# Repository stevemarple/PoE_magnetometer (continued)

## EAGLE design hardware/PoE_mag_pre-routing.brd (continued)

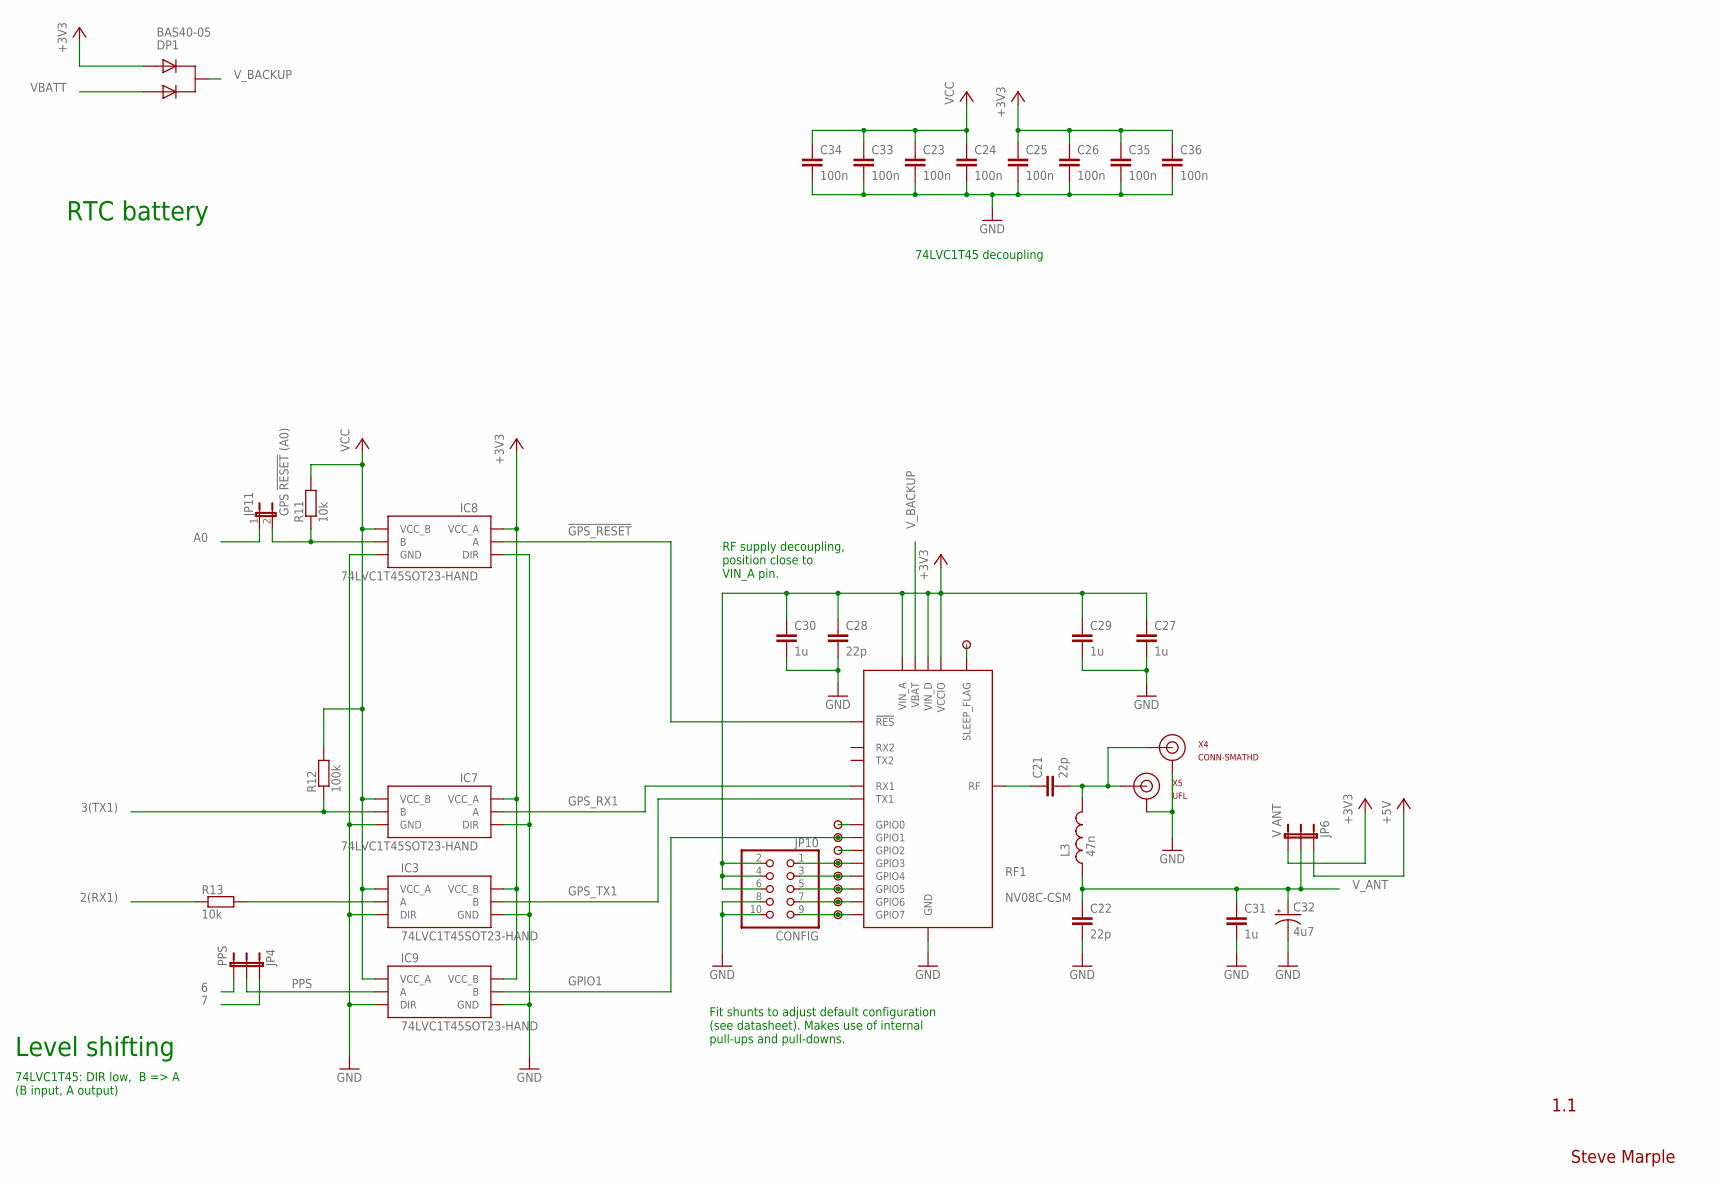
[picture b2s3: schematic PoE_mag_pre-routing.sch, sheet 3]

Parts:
C21, C22, C28: 22p; 0805-HAND
C23, C24, C25, C26, C33, C34, C35, C36: 100n; 1206-HAND
C27, C29, C30, C31: 1u; 1206-HAND
C32: 4u7; CPOL-RADIAL-10UF-25V
DP1: BAS40-05; SOT23-3-HAND
IC3, IC7, IC8, IC9: 74LVC1T45SOT23-HAND; SOT23-6-HAND
JP4: PPS; 1X03
JP6: V ANT; 1X03
JP10: CONFIG; 2X05
JP11: GPS !RESET! (A0); 1X02
L3: 47n; 0805-HAND
R11, R13: 10k; 1206-HAND
R12: 100k; 1206-HAND
RF1: NV08C-CSM; NVC08C-CSM-HAND
U$2, U$3, U$4, U$6, U$7, U$8, U$9, U$10: PAD
U$5: ?; PAD
X4: CONN-SMATHD; SMA-THD
X5: UFL; CONN-UFL-HAND-SOLDERING

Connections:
2(RX1): R13.1; also elsewhere on the board
3(TX1): IC7.4 (B), R12.1; also elsewhere on the board
6: JP4.3; also elsewhere on the board
7: JP4.1; also elsewhere on the board
!GPS_RESET: IC8.3 (A), RF1.P$25 (!RES)
+3V3: C25.1, C26.1, C27.1, C28.1, C29.1, C30.1, C35.1, C36.1, DP1.2 (A2), IC3.6 (VCC_B), IC7.1 (VCC_A), IC8.1 (VCC_A), IC9.6 (VCC_B), JP6.3, JP10.2, JP10.4, JP10.6, RF1.P$8 (VIN_A), RF1.P$26 (VIN_D), RF1.P$28 (VCCIO); also elsewhere on the board
+5V: JP6.1; also elsewhere on the board
A0: JP11.1; also elsewhere on the board
GND: C22.2, C23.2, C24.2, C25.2, C26.2, C27.2, C28.2, C29.2, C30.2, C31.2, C32.2 (-), C33.2, C34.2, C35.2, C36.2, IC3.2 (GND), IC3.5 (DIR), IC7.2 (GND), IC7.5 (DIR), IC8.2 (GND), IC8.5 (DIR), IC9.2 (GND), IC9.5 (DIR), JP10.8, JP10.10, RF1.P$3 (GND), RF1.P$9 (GND), RF1.P$10 (GND), RF1.P$11 (GND), RF1.P$12 (GND), RF1.P$13 (GND), RF1.P$14 (GND), RF1.P$16 (GND), RF1.P$17 (GND), RF1.P$18 (GND), RF1.P$19 (GND), RF1.P$22 (GND), RF1.P$24 (GND), RF1.P$27 (GND), RF1.P$29 (GND), RF1.P$34 (GND), X4.GND@0 (GND), X4.GND@1 (GND), X4.GND@2 (GND), X4.GND@3 (GND), X5.GND@0 (GND), X5.GND@1 (GND); also elsewhere on the board
GPIO0: RF1.P$20 (GPIO0), U$3.1
GPIO1: IC9.4 (B), RF1.P$2 (GPIO1), U$4.1
GPIO2: RF1.P$1 (GPIO2), U$5.1
GPIO3: JP10.1, RF1.P$6 (GPIO3), U$6.1
GPIO4: JP10.3, RF1.P$7 (GPIO4), U$7.1
GPIO5: JP10.5, RF1.P$4 (GPIO5), U$8.1
GPIO6: JP10.7, RF1.P$35 (GPIO6), U$9.1
GPIO7: JP10.9, RF1.P$5 (GPIO7), U$10.1
GPS_RX1: IC7.3 (A), RF1.P$33 (RX1)
GPS_TX1: IC3.4 (B), RF1.P$32 (TX1)
unnamed: IC8.4 (B), JP11.2, R11.1
unnamed: C21.2, L3.2, X4.SIG (SIGNAL), X5.SIGNAL
unnamed: C21.1, RF1.P$15 (RF)
unnamed: IC3.3 (A), R13.2
PPS: IC9.3 (A), JP4.2
SLEEP_FLAG: RF1.P$21 (SLEEP_FLAG), U$2.1
VBATT: DP1.1 (A1); also elsewhere on the board
VCC: C23.1, C24.1, C33.1, C34.1, IC3.1 (VCC_A), IC7.6 (VCC_B), IC8.6 (VCC_B), IC9.1 (VCC_A), R11.2, R12.2; also elsewhere on the board
V_ANT: C22.1, C31.1, C32.1 (+), JP6.2, L3.1
V_BACKUP: DP1.3 (C), RF1.P$23 (VBAT)

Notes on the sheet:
1.1
Steve Marple
Level shifting
RTC battery
74LVC1T45: DIR low, B => A (B input, A output)
RF supply decoupling, position close to VIN_A pin.
Fit shunts to adjust default configuration (see datasheet). Makes use of internal pull-ups and pull-downs.
74LVC1T45 decoupling

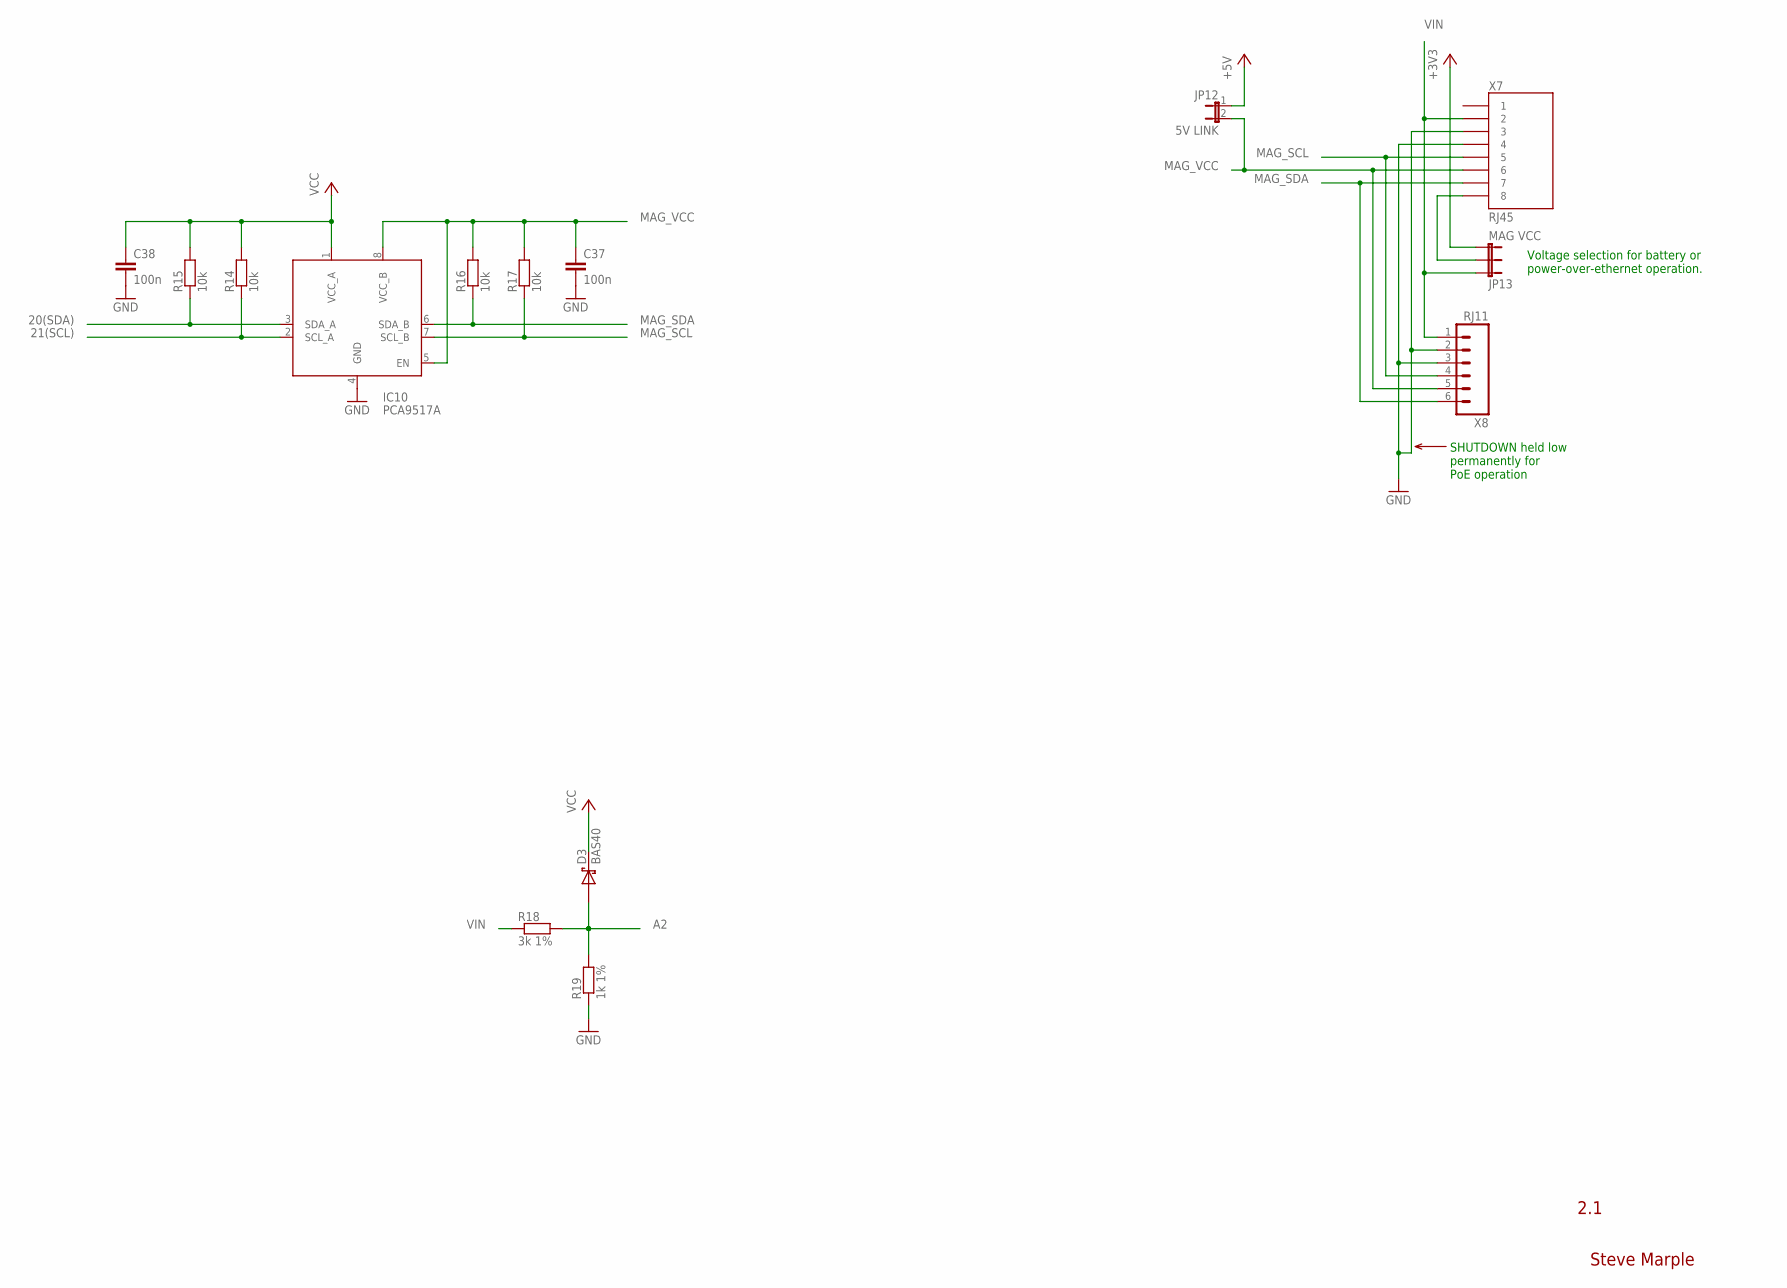
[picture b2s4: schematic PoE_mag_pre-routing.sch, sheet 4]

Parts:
C37, C38: 100n; 1206-HAND
D3: BAS40; SOT23-3-HAND
IC10: PCA9517A; SO08
JP12: 5V LINK; 1X02
JP13: MAG VCC; 1X03
R14, R15, R16, R17: 10k; 1206-HAND
R18: 3k 1%; 1206-HAND
R19: 1k 1%; 1206-HAND
X7: RJ45; RJ45-8
X8: RJ11; RJ11-6

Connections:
20(SDA): IC10.3 (SDA_A), R15.1; also elsewhere on the board
21(SCL): IC10.2 (SCL_A), R14.1; also elsewhere on the board
+3V3: JP13.3; also elsewhere on the board
+5V: JP12.1; also elsewhere on the board
A2: D3.1 (A), R18.2, R19.2; also elsewhere on the board
GND: C37.2, C38.2, IC10.4 (GND), R19.1, X7.3, X7.4, X8.2, X8.3; also elsewhere on the board
MAG_SCL: IC10.7 (SCL_B), R17.1, X7.5, X8.4
MAG_SDA: IC10.6 (SDA_B), R16.1, X7.7, X8.6
MAG_VCC: C37.1, IC10.5 (EN), IC10.8 (VCC_B), JP12.2, R16.2, R17.2, X7.6, X8.5
unnamed: JP13.2, X7.8
VCC: C38.1, D3.3 (C), IC10.1 (VCC_A), R14.2, R15.2; also elsewhere on the board
VIN: JP13.1, R18.1, X7.2, X8.1; also elsewhere on the board

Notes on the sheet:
2.1
Steve Marple
Voltage selection for battery or power-over-ethernet operation.
SHUTDOWN held low permanently for PoE operation

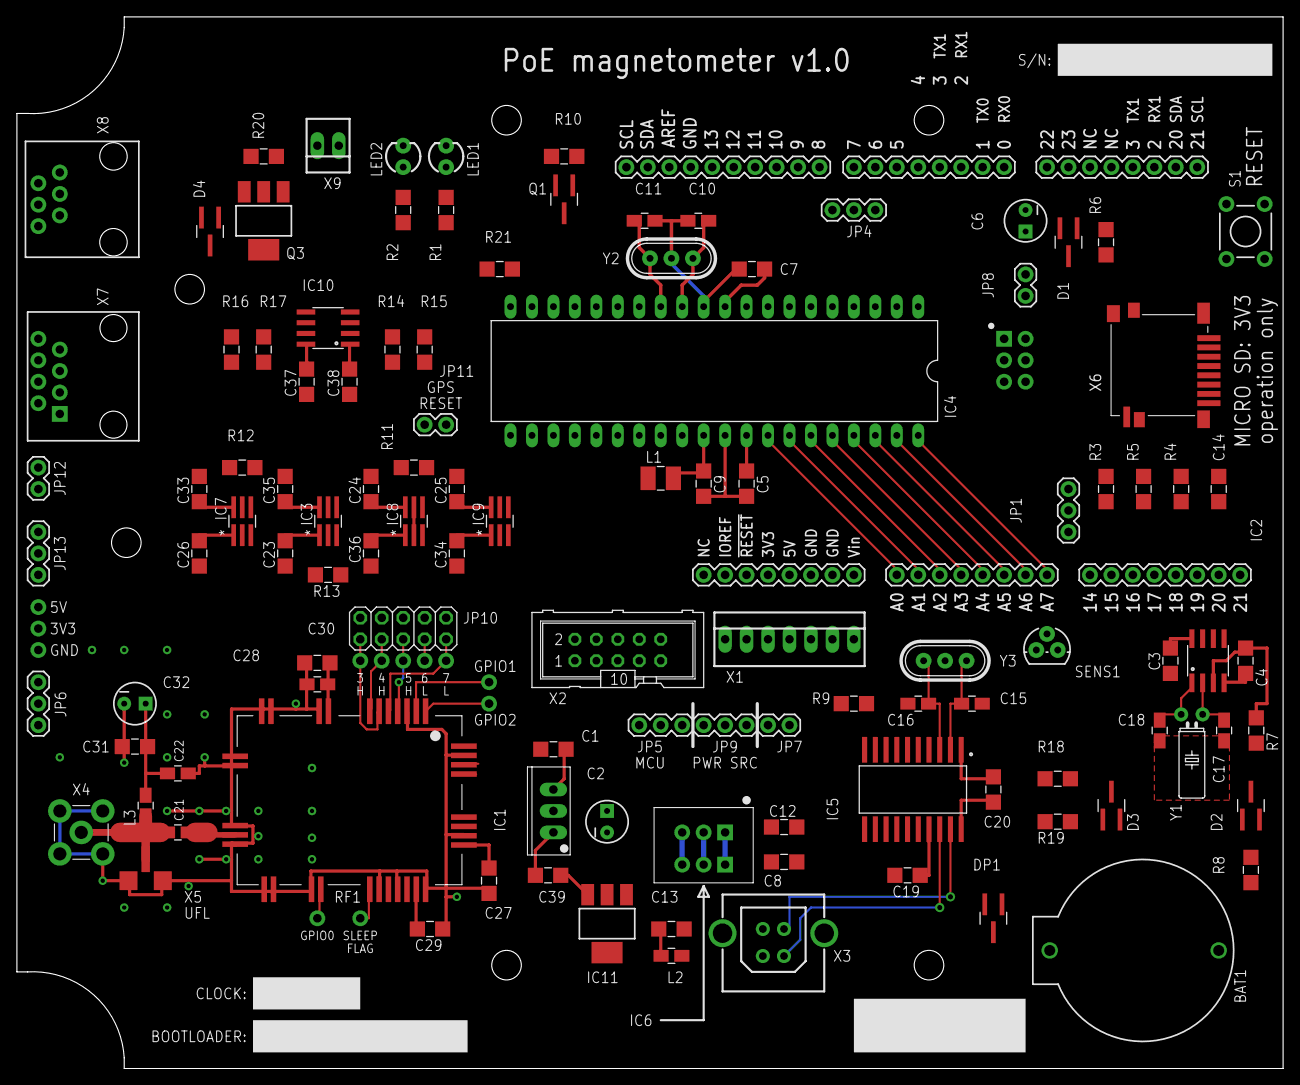
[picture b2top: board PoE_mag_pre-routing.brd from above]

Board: 2 copper layers, 149.9 x 124.5 mm, 124 parts (0 on the bottom side), 87 nets.

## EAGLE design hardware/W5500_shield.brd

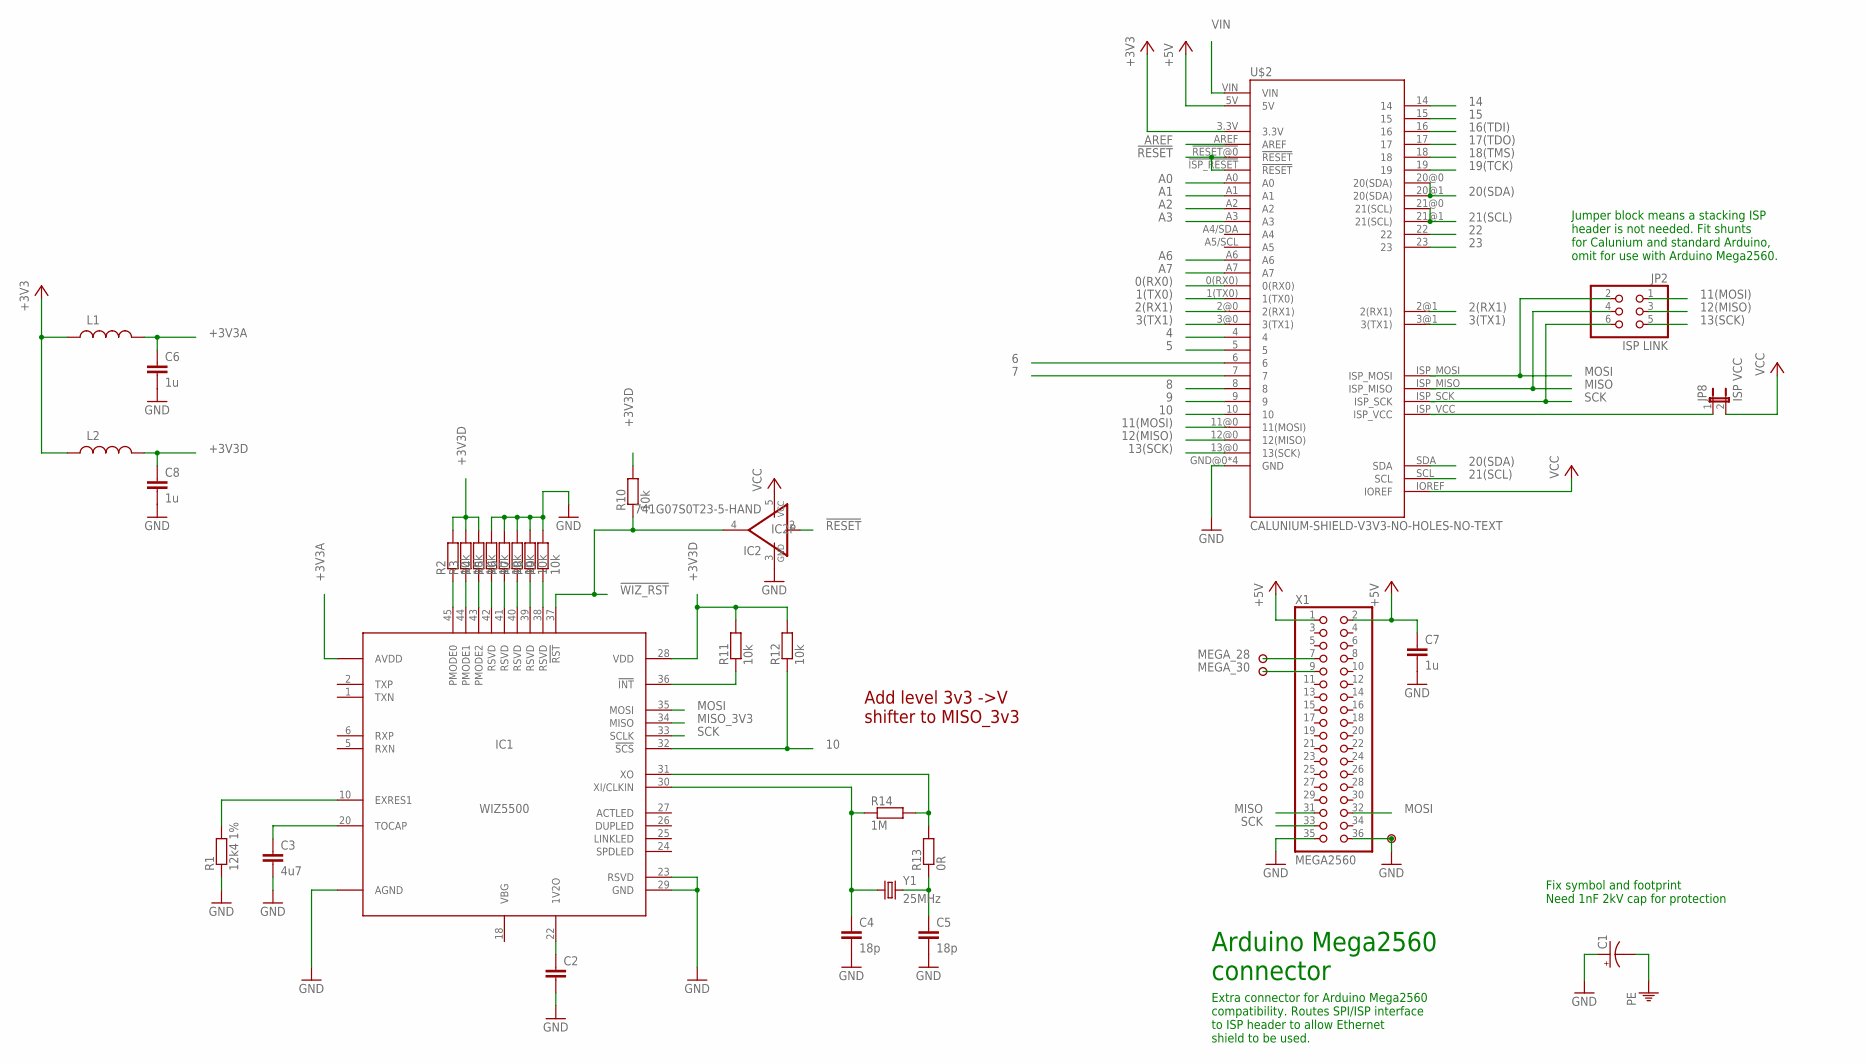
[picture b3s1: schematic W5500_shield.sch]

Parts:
C1: CAP_POL; CPOL-RADIAL-100UF-25V-150MIL
C2: C-EU1206-HAND; 1206-HAND
C3: 4u7; 1206-HAND
C4, C5: 18p; 1206-HAND
C6, C7, C8: 1u; 1206-HAND
IC1: WIZ5500; LQFP48-HAND
IC2: 741G07S0T23-5-HAND; SOT23-5-HAND
JP2: ISP LINK; 2X03
JP8: ISP VCC; 1X02
L1, L2: INDUCTOR0805-HAND; 0805-HAND
R1: 12k4 1%; 1206-HAND
R2, R3, R4, R5, R6, R7, R8, R9, R10, R11, R12: 10k; 1206-HAND
R13: 0R; 1206-HAND
R14: 1M; 1206-HAND
U$2: CALUNIUM-SHIELD-V3V3-NO-HOLES-NO-TEXT; CALUNIUM-SHIELD-NO-OUTLINE-NO-HOLES-NO-TEXT-V3
U$14, U$15, U$17: PAD
X1: MEGA2560; 2X18
Y1: 25MHz; HC49U-V

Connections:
0(RX0): U$2.0(RX0)
1(TX0): U$2.1(TX0)
2(RX1): U$2.2@0 (2(RX1)), U$2.2@1 (2(RX1))
3(TX1): U$2.3@0 (3(TX1)), U$2.3@1 (3(TX1))
4: U$2.4
5: U$2.5
6: U$2.6
7: U$2.7
8: U$2.8
9: U$2.9
10: IC1.32 (!SCS), R12.1, U$2.10
11(MOSI): JP2.1, U$2.11@0 (11(MOSI))
12(MISO): JP2.3, U$2.12@0 (12(MISO))
13(SCK): JP2.5, U$2.13@0 (13(SCK))
14: U$2.14
15: U$2.15
16(TDI): U$2.16
17(TDO): U$2.17
18(TMS): U$2.18
19(TCK): U$2.19
20(SDA): U$2.20@0 (20(SDA)), U$2.20@1 (20(SDA)), U$2.SDA
21(SCL): U$2.21@0 (21(SCL)), U$2.21@1 (21(SCL)), U$2.SCL
22: U$2.22
23: U$2.23
!RESET: IC2.2 (I), U$2.!ISP_RESET (!RESET), U$2.!RESET@0 (!RESET)
!WIZ_RST: IC1.37 (!RST), IC2.4 (O), R10.1
+3V3: L1.1, L2.1, U$2.3.3V
+3V3A: C6.1, IC1.4 (AVDD), IC1.8 (AVDD), IC1.11 (AVDD), IC1.15 (AVDD), IC1.17 (AVDD), IC1.21 (AVDD), L1.2
+3V3D: C8.1, IC1.28 (VDD), L2.2, R2.2, R3.2, R4.2, R10.2, R11.2, R12.2
+5V: C7.1, U$2.5V, X1.1, X1.2
A0: U$2.A0
A1: U$2.A1
A2: U$2.A2
A3: U$2.A3
A6: U$2.A6
A7: U$2.A7
AREF: U$2.AREF
GND: C1.1 (+), C2.2, C3.2, C4.2, C5.2, C6.2, C7.2, C8.2, IC1.3 (AGND), IC1.9 (AGND), IC1.14 (AGND), IC1.16 (AGND), IC1.19 (AGND), IC1.23 (RSVD), IC1.29 (GND), IC1.48 (AGND), IC2.3 (GND), R1.1, R5.2, R6.2, R7.2, R8.2, R9.2, U$2.GND@0 (GND), U$2.GND@1 (GND), U$2.GND@2 (GND), U$2.GND@3 (GND), U$17.1, X1.35, X1.36
MEGA_28: U$14.1, X1.7
MEGA_30: U$15.1, X1.9
MISO: JP2.4, U$2.ISP_MISO, X1.31
MISO_3V3: IC1.34 (MISO)
MOSI: IC1.35 (MOSI), JP2.2, U$2.ISP_MOSI, X1.32
unnamed: C4.1, IC1.30 (XI/CLKIN), R14.1, Y1.1
unnamed: C2.1, IC1.22 (1V2O)
unnamed: C3.1, IC1.20 (TOCAP)
unnamed: IC1.10 (EXRES1), R1.2
unnamed: IC1.45 (PMODE0), R2.1
unnamed: IC1.44 (PMODE1), R3.1
unnamed: IC1.43 (PMODE2), R4.1
unnamed: IC1.42 (RSVD), R5.1
unnamed: IC1.41 (RSVD), R6.1
unnamed: IC1.40 (RSVD), R7.1
unnamed: IC1.39 (RSVD), R8.1
unnamed: IC1.38 (RSVD), R9.1
unnamed: IC1.31 (XO), R13.2, R14.2
unnamed: IC1.36 (!INT), R11.1
unnamed: C5.1, R13.1, Y1.2
unnamed: JP8.1, U$2.ISP_VCC
PE: C1.2 (-)
SCK: IC1.33 (SCLK), JP2.6, U$2.ISP_SCK, X1.33
VCC: IC2.5 (VCC), JP8.2, U$2.IOREF
VIN: U$2.VIN

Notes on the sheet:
Fix symbol and footprint Need 1nF 2kV cap for protection
Add level 3v3 ->V shifter to MISO_3v3
Jumper block means a stacking ISP header is not needed. Fit shunts for Calunium and standard Arduino, omit for use with Arduino Mega2560.
Arduino Mega2560 connector
Extra connector for Arduino Mega2560 compatibility. Routes SPI/ISP interface to ISP header to allow Ethernet shield to be used.

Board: 2 copper layers, 34 parts (0 on the bottom side), 37 nets, no tracks yet.

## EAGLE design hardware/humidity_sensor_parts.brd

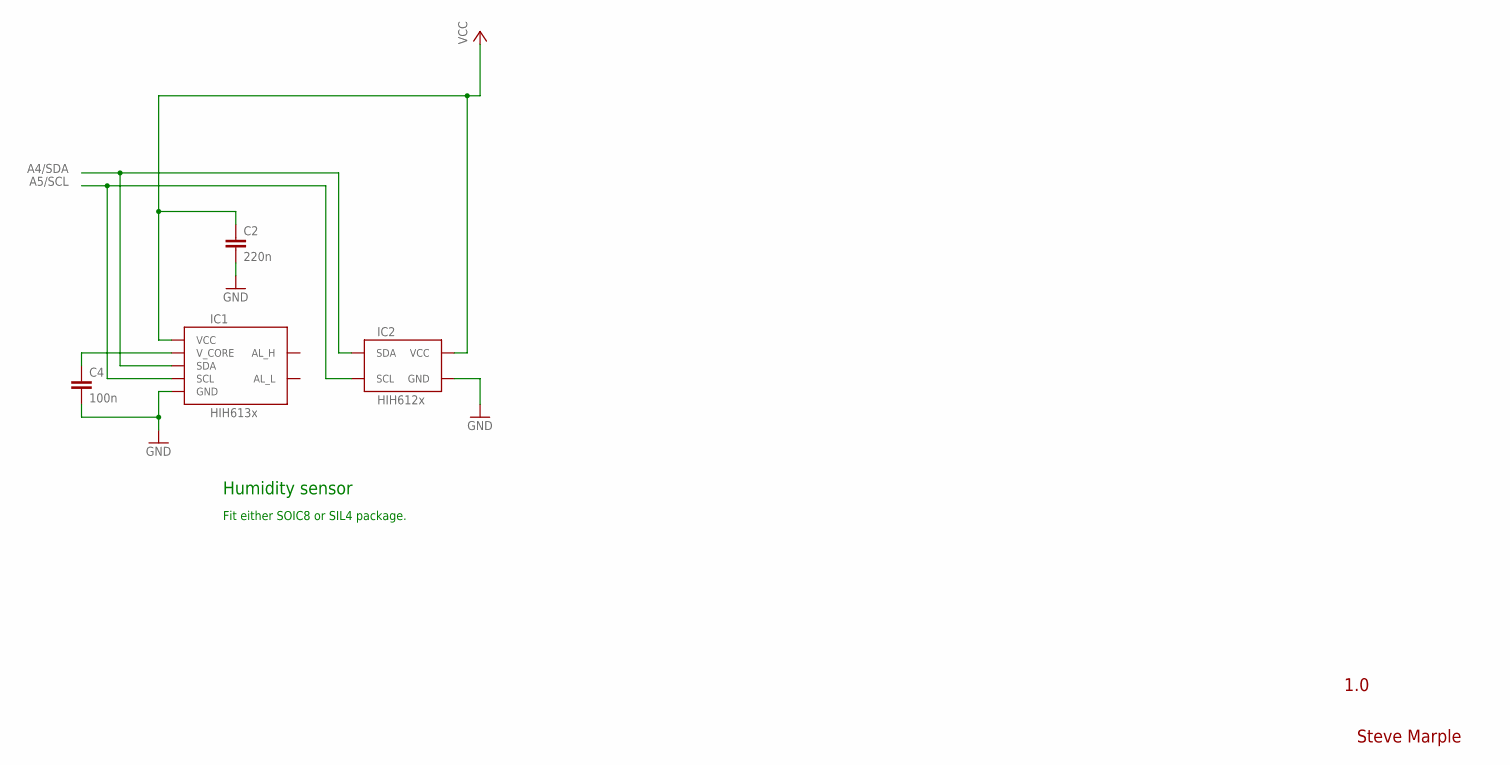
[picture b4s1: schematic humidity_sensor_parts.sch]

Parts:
C2: 220n; CAP-PTH-SMALL
C4: 100n; CAP-PTH-SMALL
IC1: HIH613x; SO08
IC2: HIH612x; SIL04

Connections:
A4/SDA: IC1.4 (SDA), IC2.4 (SDA)
A5/SCL: IC1.3 (SCL), IC2.3 (SCL)
GND: C2.2, C4.2, IC1.2 (GND), IC2.2 (GND)
VCC: C2.1, IC1.8 (VCC), IC2.1 (VCC)
V_CORE: C4.1, IC1.1 (V_CORE)

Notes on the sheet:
Humidity sensor
Fit either SOIC8 or SIL4 package.
1.0
Steve Marple

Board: 2 copper layers, 4 parts (2 on the bottom side), 5 nets, no tracks yet.

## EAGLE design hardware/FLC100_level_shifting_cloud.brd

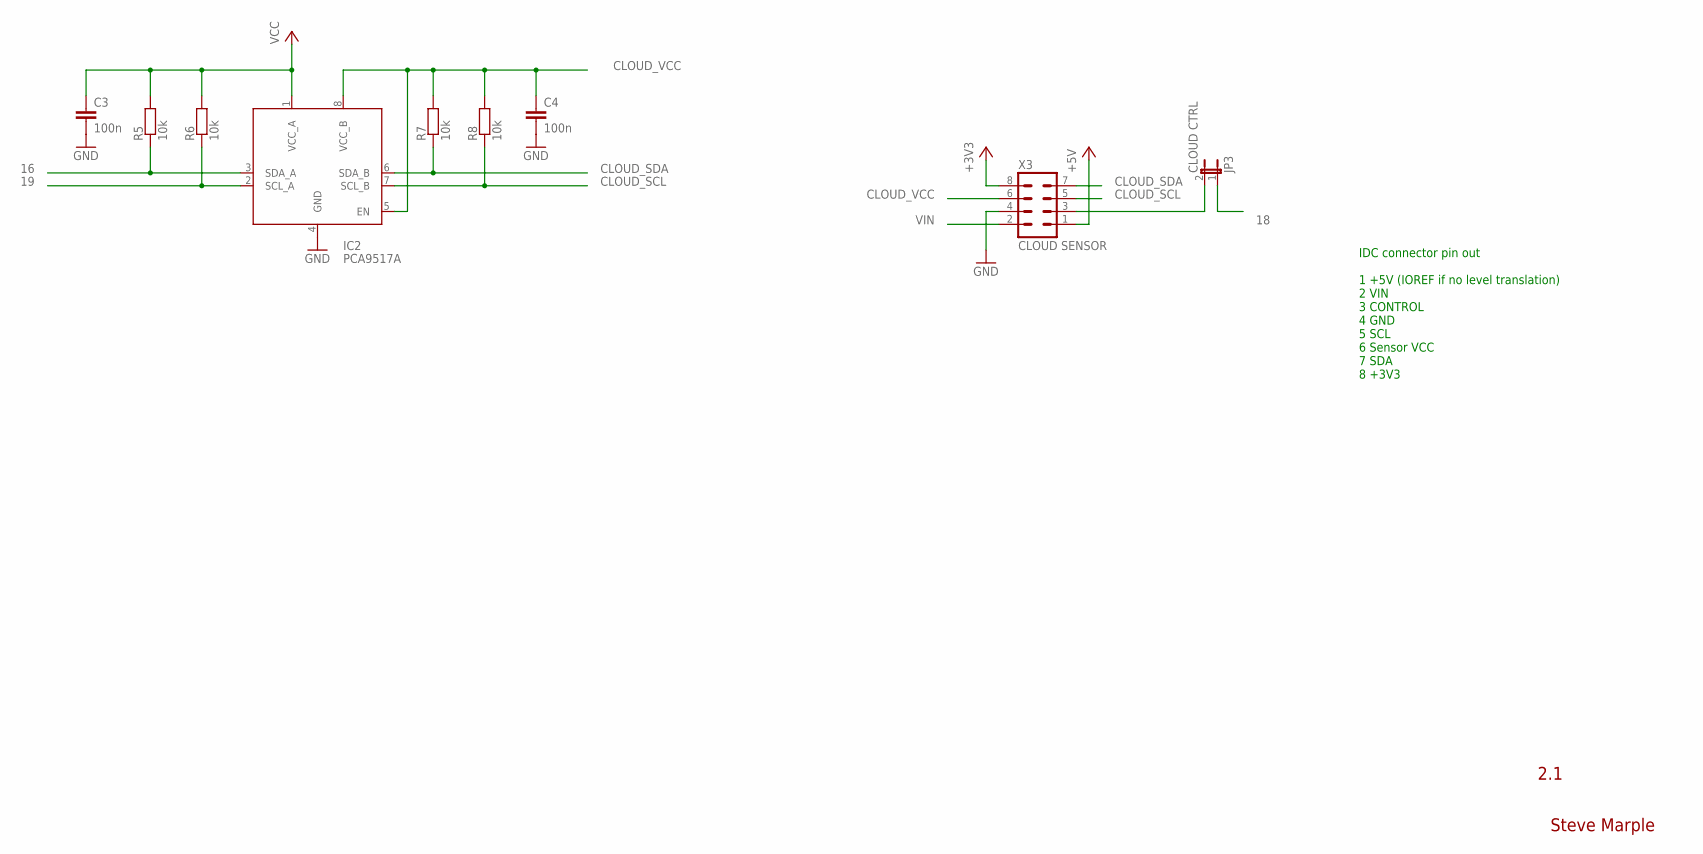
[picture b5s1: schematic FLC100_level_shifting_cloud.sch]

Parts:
C3, C4: 100n; 1206-HAND
IC2: PCA9517A; SO08
JP3: CLOUD CTRL; 1X02
R5, R6, R7, R8: 10k; 1206-HAND
X3: CLOUD SENSOR; ML8

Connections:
16: IC2.3 (SDA_A), R5.1
18: JP3.1
19: IC2.2 (SCL_A), R6.1
+3V3: X3.8
+5V: X3.1
CLOUD_SCL: IC2.7 (SCL_B), R8.1, X3.5
CLOUD_SDA: IC2.6 (SDA_B), R7.1, X3.7
CLOUD_VCC: C4.1, IC2.5 (EN), IC2.8 (VCC_B), R7.2, R8.2, X3.6
GND: C3.2, C4.2, IC2.4 (GND), X3.4
unnamed: JP3.2, X3.3
VCC: C3.1, IC2.1 (VCC_A), R5.2, R6.2
VIN: X3.2

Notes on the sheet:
2.1
Steve Marple
IDC connector pin out 1 +5V (IOREF if no level translation) 2 VIN 3 CONTROL 4 GND 5 SCL 6 Sensor VCC 7 SDA 8 +3V3

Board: 2 copper layers, 9 parts (0 on the bottom side), 8 nets, no tracks yet.

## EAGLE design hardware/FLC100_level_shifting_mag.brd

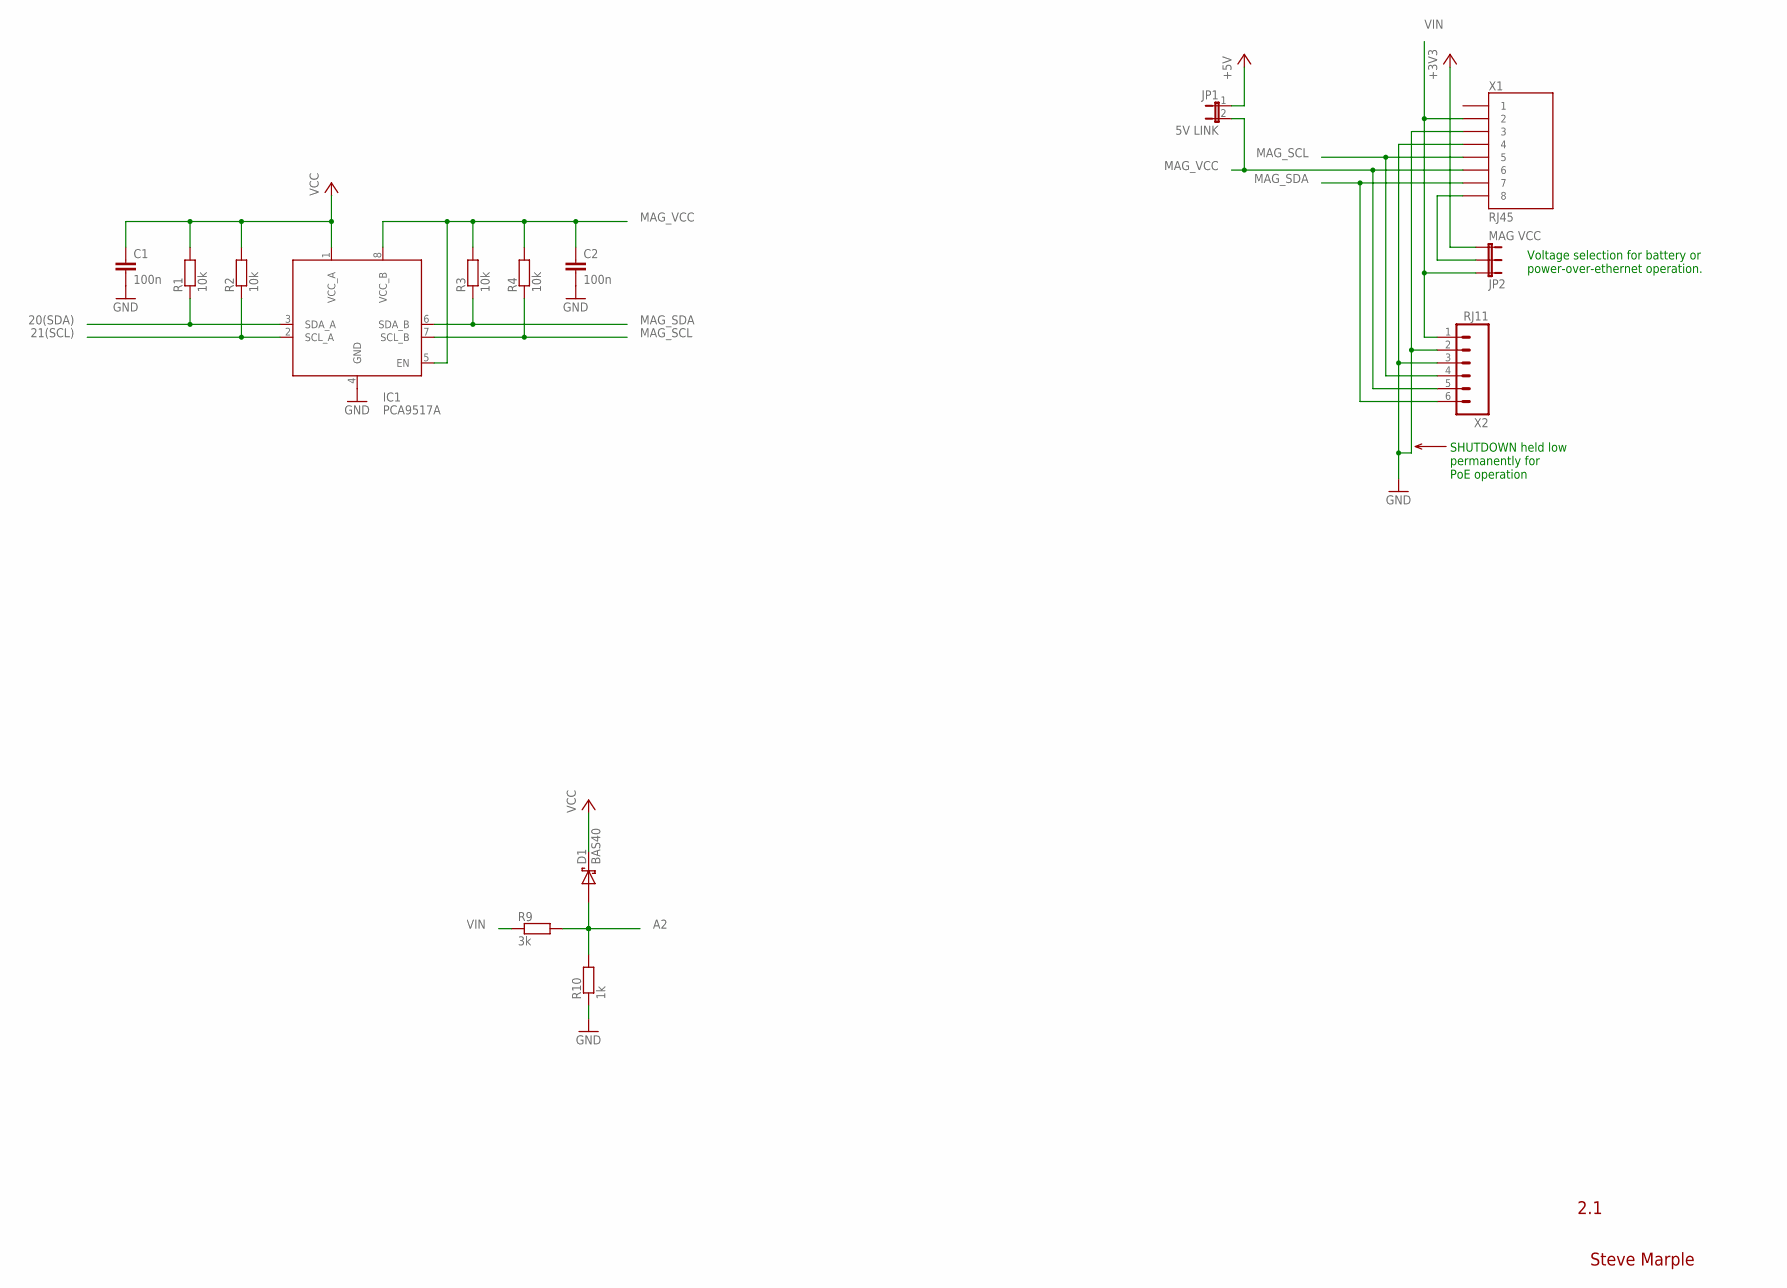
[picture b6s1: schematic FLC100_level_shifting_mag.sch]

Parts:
C1, C2: 100n; 1206-HAND
D1: BAS40; SOT23-3-HAND
IC1: PCA9517A; SO08
JP1: 5V LINK; 1X02
JP2: MAG VCC; 1X03
R1, R2, R3, R4: 10k; 1206-HAND
R9: 3k; 1206-HAND
R10: 1k; 1206-HAND
X1: RJ45; RJ45-8
X2: RJ11; RJ11-6

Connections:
20(SDA): IC1.3 (SDA_A), R1.1
21(SCL): IC1.2 (SCL_A), R2.1
+3V3: JP2.3
+5V: JP1.1
A2: D1.1 (A), R9.2, R10.2
GND: C1.2, C2.2, IC1.4 (GND), R10.1, X1.3, X1.4, X2.2, X2.3
MAG_SCL: IC1.7 (SCL_B), R4.1, X1.5, X2.4
MAG_SDA: IC1.6 (SDA_B), R3.1, X1.7, X2.6
MAG_VCC: C2.1, IC1.5 (EN), IC1.8 (VCC_B), JP1.2, R3.2, R4.2, X1.6, X2.5
unnamed: JP2.2, X1.8
VCC: C1.1, D1.3 (C), IC1.1 (VCC_A), R1.2, R2.2
VIN: JP2.1, R9.1, X1.2, X2.1

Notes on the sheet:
2.1
Steve Marple
Voltage selection for battery or power-over-ethernet operation.
SHUTDOWN held low permanently for PoE operation

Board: 2 copper layers, 14 parts (0 on the bottom side), 10 nets, no tracks yet.

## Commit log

2015-10-15 Add hardware files
2015-10-16 Misc changes
2015-10-19 Add new board versions
2015-10-19 Add level shifting circuit
2015-10-20 Layout fixes
2015-10-20 Add magnetometer level shifting
2015-10-21 Add schematics and boards for various modules
2015-10-29 Add Fibox box outline
2015-10-29 Update W5500 shield
2015-11-06 Update enclosure outline, move components
2015-11-09 Add updated hardware version
2015-11-09 Update enclosure outline
2015-11-09 Update enclosure restrictions
2015-11-10 Fix silkscreen text
2015-11-11 Use TO220 package of LD1117
2015-11-11 Board layout changes
2015-11-12 Add Powerpax reg option, move RJ11/45 connectors
2015-11-13 Minor changes
2015-11-13 Rotate RJ11, RJ45 by 180 degrees
2015-11-16 Version before routing, and possible final routing
2015-11-17 Improve layout and track spacing
2015-11-17 Fix incorrect USB power filtering
2015-11-17 Routed layout with no DRC warnings
2015-11-18 Minor changes for ground pour
2015-11-18 Add Gerber files
2015-11-18 Remove intermediate alternative versions
2015-11-18 Always power LM61 and swap to SOT23 package
2015-11-18 Update Gerber files
2015-11-18 Improve decoupling for voltage regulators
2015-11-19 Renumber components
2015-11-19 Move battery holder
    Move to create more room so that alternative versions can be used.
2016-01-14 Update crystal value
2016-01-14 Increase diameter of mounting holes
2016-01-14 Increase spacing around thermal reliefs
2016-01-14 Increase dia of mounting holes, increase thermal reliefs
2016-01-14 Add pads for support wire over 32768Hz crystal
2016-01-22 Increare mounting holes to 4mm diameter
2016-01-22 Reroute bottom layer tracks to avoid lugs on box
    Also use 4mm diameter mounting holes
2016-01-29 Add cap for RFI suppression across fan, minor track layout changes
2016-01-31 Increase pad size for CR2032 battery holder
2016-02-07 Show alternative build configurations more clearly
    Move TO-220 variant of LD1117V33 to show it is the alternative
    fit. Use short dashed lines to connect all optional/variant
    components. Add "*" suffix to component values which are
    optional/variants to ease construction o the standard version. Minor
    silkscreen changes on board to accomodate longer text.
2016-02-08 Add decoupling for supply voltage measurement
2016-02-08 Moving design files into specific v1.1 directory
2016-02-08 Add version 1.0 files from commit ca8d9ab29a9d674b81ec7ae46e74108e80dcdbfc
2016-02-08 Remove unwanted file
2016-02-08 Use semantic versioning for hardware
    Latest revision termed v1.0.1, reflecting that it has mainly cosmetic
    changes. Only electrical change is addition of decoupling capacitor
    for ADC measurement of supply voltage.
2016-02-08 Add drilling details for Fibox plastic box
2016-02-08 Fix incorrect version number on schematic
2016-02-08 Use semantic versioning on PCB
2016-02-08 Add v1.0.1 Gerber files
2016-02-08 Changed ignored Gerber files
2016-11-02 Renamed with version number
2016-11-02 Add drawings used for enclosure with original prototype
2021-01-10 Add instructions for GNSS module firmware upgrade
2021-03-28 Add LICENSE
    Using Creative Commons Attribution-ShareAlike 3.0 Unported License, as this is a derivation of Calunium, https://github.com/stevemarple/Calunium
2021-03-28 Update firmware upgrade information
    Reformat and fix typos.
